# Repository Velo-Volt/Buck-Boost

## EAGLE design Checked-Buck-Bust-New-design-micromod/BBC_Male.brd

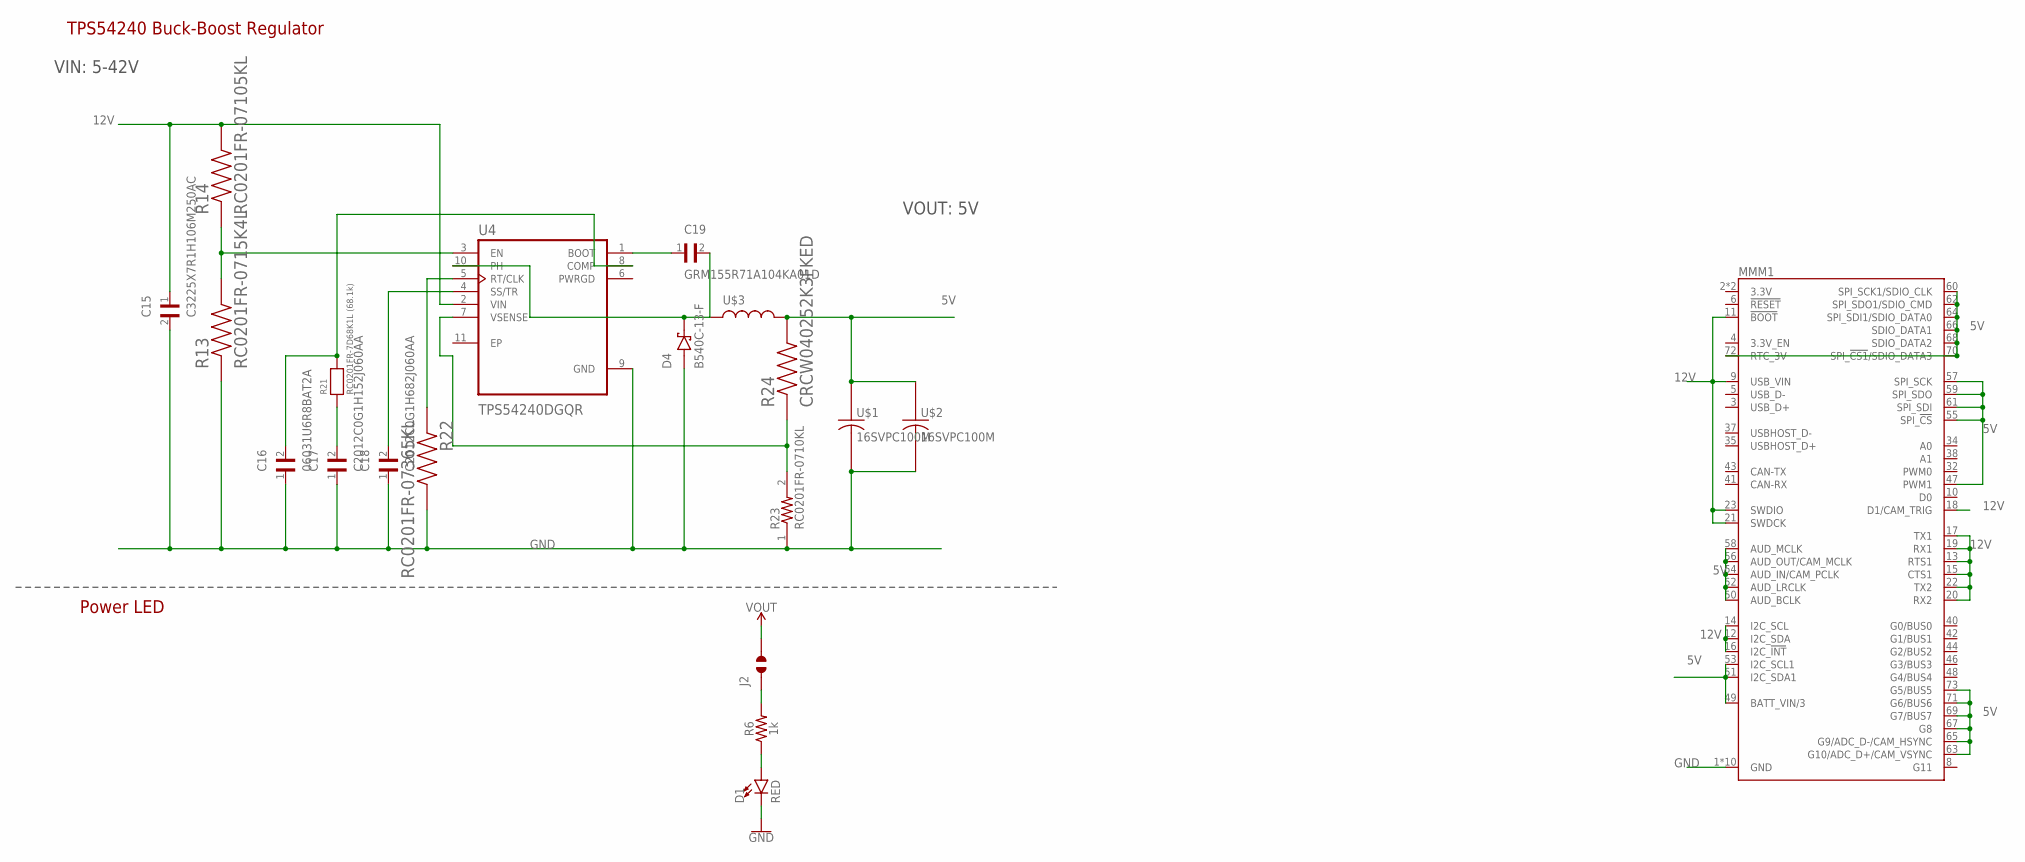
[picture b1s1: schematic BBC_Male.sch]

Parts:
C15: C3225X7R1H106M250AC; CAPC3225X280N
C16: 06031U6R8BAT2A; CAPC1507X91N
C17: C2012C0G1H152J060AA; CAPC2012X75N
C18: C2012C0G1H682J060AA; CAPC2012X75N
C19: GRM155R71A104KA01D; CAPC1005X55N
D1: RED; LED-0603
D4: B540C-13-F; DIOM6959X245N
J2: JUMPER_SOLDER_1X2
MMM1: MICROMOD_4222_MALE
R6: 1k; 0603
R13: RC0201FR-0715K4L; RESC0603X26N
R14: RC0201FR-07105KL; RESC0603X26N
R21: RC0201FR-7D68K1L (68.1k); _0603
R22: RC0201FR-07365KL; RESC0603X26N
R23: RC0201FR-0710KL; RESC0603X26N
R24: CRCW040252K3FKED; RESC1005X40N
U4: TPS54240DGQR; IC_XTR111AIDGQR
U$1, U$2: 16SVPC100M; CAPAE0607X600N
U$3: MSS1260

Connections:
5V: J2.2, MMM1.47 (PWM1), MMM1.49 (BATT_VIN/3), MMM1.50 (AUD_BCLK), MMM1.51 (I2C_SDA1), MMM1.52 (AUD_LRCLK), MMM1.53 (I2C_SCL1), MMM1.54 (AUD_IN/CAM_PCLK), MMM1.55 (SPI_!CS!), MMM1.56 (AUD_OUT/CAM_MCLK), MMM1.57 (SPI_SCK), MMM1.58 (AUD_MCLK), MMM1.59 (SPI_SDO), MMM1.60 (SPI_SCK1/SDIO_CLK), MMM1.61 (SPI_SDI), MMM1.62 (SPI_SDO1/SDIO_CMD), MMM1.63 (G10/ADC_D+/CAM_VSYNC), MMM1.64 (SPI_SDI1/SDIO_DATA0), MMM1.65 (G9/ADC_D-/CAM_HSYNC), MMM1.66 (SDIO_DATA1), MMM1.67 (G8), MMM1.68 (SDIO_DATA2), MMM1.69 (G7/BUS7), MMM1.70 (SPI_!CS1!/SDIO_DATA3), MMM1.71 (G6/BUS6), MMM1.72 (RTC_3V), MMM1.73 (G5/BUS5), R24.2, U$1.+, U$2.+, U$3.P$1
12V: C15.1, MMM1.9 (USB_VIN), MMM1.11 (!BOOT!), MMM1.12 (I2C_SDA), MMM1.13 (RTS1), MMM1.14 (I2C_SCL), MMM1.15 (CTS1), MMM1.16 (I2C_!INT!), MMM1.17 (TX1), MMM1.18 (D1/CAM_TRIG), MMM1.19 (RX1), MMM1.20 (RX2), MMM1.21 (SWDCK), MMM1.22 (TX2), MMM1.23 (SWDIO), R14.2, U4.2 (VIN)
GND: C15.2, C16.1, C17.1, C18.1, D1.C, D4.A, MMM1.1 (GND), MMM1.7 (GND), MMM1.33 (GND), MMM1.36 (GND), MMM1.39 (GND), MMM1.45 (GND), MMM1.75 (GND), MMM1.GND1 (GND), MMM1.GND2 (GND), MMM1.GND3 (GND), R13.1, R22.2, R23.1, U4.9 (GND), U$1.-, U$2.-
unnamed: J2.1, R6.2
unnamed: D1.A, R6.1
unnamed: C19.1, U4.1 (BOOT)
unnamed: C17.2, R21.1
unnamed: R13.2, R14.1, U4.3 (EN)
unnamed: C16.2, R21.2, U4.8 (COMP)
unnamed: R23.2, R24.1, U4.7 (VSENSE)
unnamed: C19.2, D4.C (K), U4.10 (PH), U$3.P$2
unnamed: C18.2, U4.4 (SS/TR)
unnamed: R22.1, U4.5 (RT/CLK)

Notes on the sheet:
TPS54240 Buck-Boost Regulator
VIN: 5-42V
VOUT: 5V
Power LED

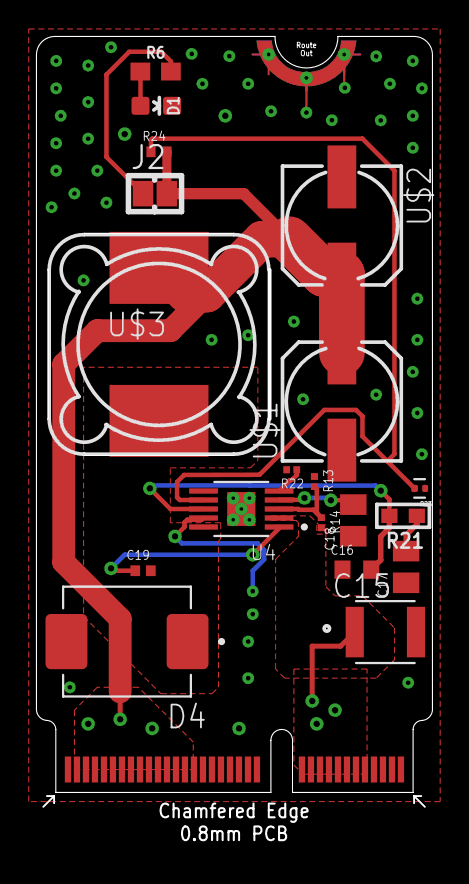
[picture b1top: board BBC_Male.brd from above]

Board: 2 copper layers, 21.8 x 44.9 mm, 20 parts (0 on the bottom side), 13 nets.

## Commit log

2021-01-26 Create Buck-Boost-Newdesign-Micromod-Checked
2021-01-26 Checked.txt
2021-01-26 dummy.txt
2021-01-26 Create Checked

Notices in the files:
parts and their libraries:
SparkFun-Resistors: Licensing: Creative Commons ShareAlike 4.0 International - https://creativecommons.org/licenses/by-sa/4.0
microbuilder: This work is placed in the public domain, and may be freely used for commercial and non-commercial work with the following conditions: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
